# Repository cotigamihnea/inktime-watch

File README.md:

# InkTime Smartwatch - Proiect Hardware

Acesta este repository-ul oficial pentru dezvoltarea hardware a proiectului InkTime, un smartwatch bazat pe tehnologia E-Paper și procesorul nRF52840, optimizat pentru un consum redus de energie.

---

## 1. Diagramă Bloc

---

## 2. Bill of Materials (BOM) Principale

Mai jos sunt listate componentele integrate (IC) principale folosite în designul acestui smartwatch. Fișierul BOM complet cu toate componentele pasive (rezistențe, condensatoare) se găsește în folderul `Manufacturing`.

| Componentă / Modul | Rol în Sistem | JLC Parts Link | Datasheet |
| :--- | :--- | :--- | :--- |
| **nRF52840-QIAA** | Microcontroller Principal (BLE 5.0) | [C209930](https://jlcpcb.com/partdetail/Nordic_Semiconductor-nRF52840_QIAAR/C209930) | [Datasheet nRF52840](https://infocenter.nordicsemi.com/pdf/nRF52840_PS_v1.1.pdf) |
| **BQ25180YBGR** | Li-Ion Battery Charger (PMIC) | [C3005391](https://jlcpcb.com/partdetail/TexasInstruments-BQ25180YBGR/C3005391) | [Datasheet BQ25180](https://www.ti.com/lit/ds/symlink/bq25180.pdf) |
| **MAX17048G+T10** | Fuel Gauge (Monitorizare Baterie) | [C137599](https://jlcpcb.com/partdetail/Maxim_Integrated-MAX17048GT10/C137599) | [Datasheet MAX17048](https://datasheets.maximintegrated.com/en/ds/MAX17048-MAX17049.pdf) |
| **BMA421** | IMU / Accelerometru (Pedometer) | [C456073](https://jlcpcb.com/partdetail/Bosch-BMA421/C456073) | [Datasheet BMA421](https://www.bosch-sensortec.com/media/boschsensortec/downloads/datasheets/bst-bma421-fl000.pdf) |
| **503480-2400** | Conector Display E-Paper (24 pini) | [C265215](https://jlcpcb.com/partdetail/Molex-5034802400/C265215) | [Datasheet Molex](https://www.molex.com/pdm_docs/sd/5034802400_sd.pdf) |

---

## 3. Descrierea Funcționalității Hardware

Proiectul InkTime este gândit ca un wearable ultra-low-power. Arhitectura hardware este împărțită în următoarele module principale:

* **Unitatea de Procesare și Comunicație (nRF52840):** Este "creierul" plăcii. Acesta conține un nucleu ARM Cortex-M4F și un modul radio Bluetooth Low Energy (BLE 5.0). Microcontroller-ul gestionează toate perifericele și permite sincronizarea datelor cu un smartphone.
* **Afișajul (E-Paper Display):** Conectat printr-o interfață **SPI**, display-ul E-paper a fost ales pentru consumul său zero de energie în starea de repaus (consumă curent doar la refresh-ul ecranului). Circuitul său include o sursă de tensiune dedicată, cu o bobină și diode, comandată de un tranzistor DMG2305UX, pentru a-i asigura tensiunile specifice de operare.
* **Managementul Energiei (Power Management):** * **BQ25180:** Se ocupă de încărcarea sigură a bateriei Li-Po de la mufa USB (5V), setând curenți mici de încărcare adecvați bateriilor de smartwatch.
    * **MAX17048 (Fuel Gauge):** Citește tensiunea bateriei și calculează procentul (State of Charge - SoC) folosind algoritmul ModelGauge. Ambele comunică cu nRF-ul prin magistrala **I2C**.
* **Senzori și Haptic:** Accelerometrul **BMA421** este folosit pentru detectarea mișcării (ex: ridicarea mâinii pentru a aprinde ecranul) și numărarea pașilor, comunicând tot prin **I2C**. Pentru feedback tactil s-a integrat un driver haptic.
* **Considerații de Consum:** Designul este centrat pe eficiență. nRF52840 va sta majoritatea timpului în *Deep Sleep* (câțiva microamperi), trezindu-se doar la întreruperi generate de BMA421 (mișcare) sau la intervale regulate pentru a actualiza ecranul prin SPI.

---

## 4. Pinout nRF52840 (Alocarea Pinilor)

Microcontroller-ul comunică cu restul modulelor folosind interfețe digitale standardizate. Magistrala I2C este partajată pentru a economisi pini.

| Periferic / Modul | Pini nRF52840 Alocați | Interfață | Motiv / Funcție |
| :--- | :--- | :--- | :--- |
| **Magistrala I2C (Comună)** | `P0.11` (SDA), `P0.12` (SCL) | I2C | Folosită pentru BQ25180 (Charger), MAX17048 (Baterie) și BMA421 (IMU). I2C permite legarea mai multor senzori pe doar 2 pini fizici, reducând complexitatea rutării. |
| **BMA421 (Senzor Mișcare)**| `P0.13` (INT1) | GPIO | Pin de întrerupere pentru a „trezi” procesorul din sleep când utilizatorul face o mișcare bruscă. |
| **Display E-Paper** | `P1.01` (MOSI), `P1.02` (SCK), `P1.03` (CS) | SPI | Interfață de mare viteză unidirecțională pentru a trimite pixelii către ecran rapid. |
| **Control E-Paper** | `P1.04` (DC), `P1.05` (RST), `P1.06` (BUSY)| GPIO | Pini de control pentru stările ecranului (Data/Command, Reset și monitorizarea stării de Busy în timpul refresh-ului). |
| **Alimentare E-Paper** | `P0.06` | GPIO | Controlează tranzistorul care taie complet alimentarea ecranului când nu este folosit, salvând energie. |

*(Notă: Pinii exacți au fost aleși pentru a facilita cel mai scurt drum de rutare (Placement Optimization) pe PCB).*

---

## 5. Design Log & Renders

**Jurnal de Design:**
Proiectarea PCB-ului a presupus mai multe provocări:
1.  **Placement:** Componentele au fost grupate în "cartiere" logice: RF-ul sus în jurul antenei pentru a minimiza interferențele, IC-urile de Power Management lângă conectorul bateriei/USB, iar componentele digitale centralizate în jurul procesorului nRF52840.
2.  **Routing:** Datorită densității mari de pe o placă cu factor de formă mic (Smartwatch), am utilizat un mix de rutare manuală pentru traseele sensibile și Autorouter pentru optimizarea conexiunilor logice, obținând o rată de conectare excelentă pentru un sistem cu doar 2 straturi.

**Randări PCB:**

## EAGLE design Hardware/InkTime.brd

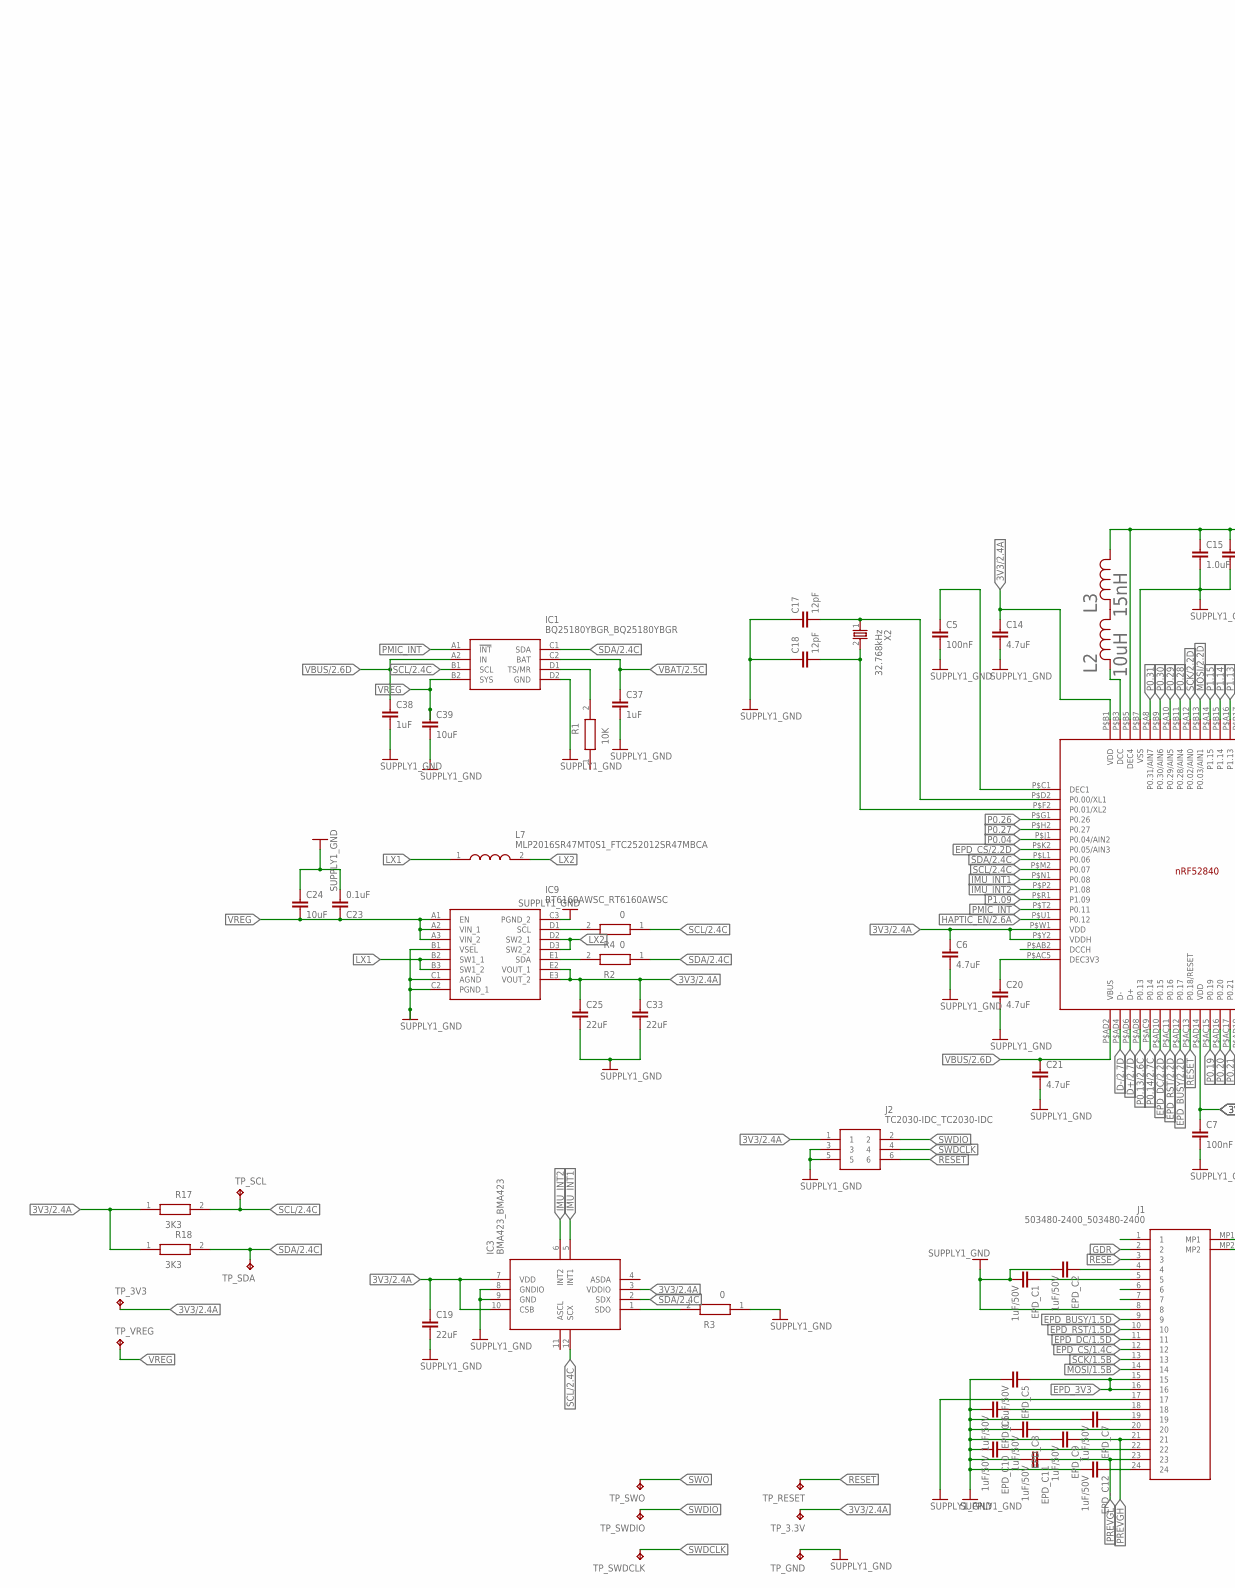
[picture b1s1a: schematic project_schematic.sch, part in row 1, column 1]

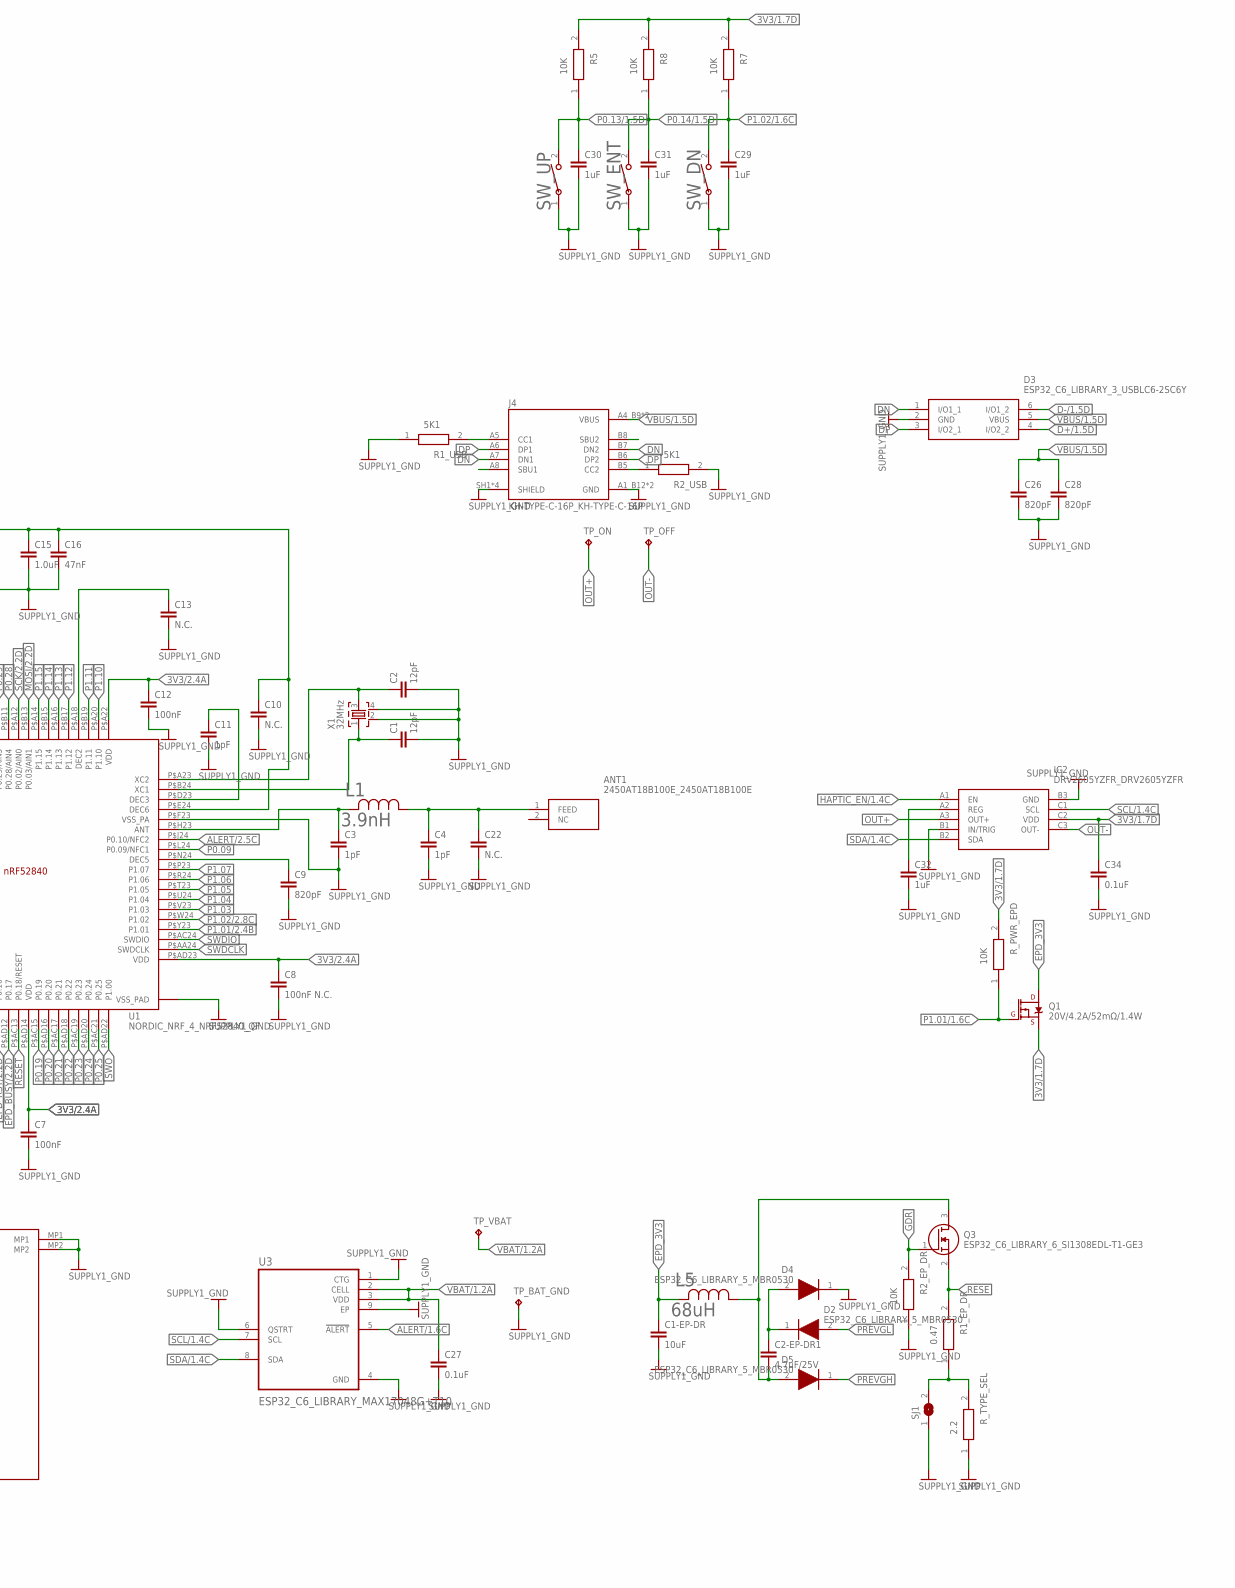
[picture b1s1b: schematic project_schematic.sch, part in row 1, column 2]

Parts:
ANT1: 2450AT18B100E_2450AT18B100E; 2450AT18B100E_ANTC3216X140N
C1, C2, C17, C18: 12pF; ESP32_C6_LIBRARY_1_ESP32_WROVER_EAGLE-LTSPICE_C0402
C1-EP-DR, C24, C39: 10uF; ESP32_C6_LIBRARY_1_ESP32_WROVER_EAGLE-LTSPICE_C0402
C2-EP-DR1: 4.7uF/25V; ESP32_C6_LIBRARY_1_ESP32_WROVER_EAGLE-LTSPICE_C0402
C3, C4, C11: 1pF; ESP32_C6_LIBRARY_1_ESP32_WROVER_EAGLE-LTSPICE_C0402
C5, C7, C12: 100nF; ESP32_C6_LIBRARY_1_ESP32_WROVER_EAGLE-LTSPICE_C0402
C6, C14, C20, C21: 4.7uF; ESP32_C6_LIBRARY_1_ESP32_WROVER_EAGLE-LTSPICE_C0402
C8: 100nF N.C.; ESP32_C6_LIBRARY_1_ESP32_WROVER_EAGLE-LTSPICE_C0402
C9, C26, C28: 820pF; ESP32_C6_LIBRARY_1_ESP32_WROVER_EAGLE-LTSPICE_C0402
C10, C13, C22: N.C.; ESP32_C6_LIBRARY_1_ESP32_WROVER_EAGLE-LTSPICE_C0402
C15: 1.0uF; ESP32_C6_LIBRARY_1_ESP32_WROVER_EAGLE-LTSPICE_C0402
C16: 47nF; ESP32_C6_LIBRARY_1_ESP32_WROVER_EAGLE-LTSPICE_C0402
C19, C25, C33: 22uF; ESP32_C6_LIBRARY_1_ESP32_WROVER_EAGLE-LTSPICE_C0402
C23, C27, C34: 0.1uF; ESP32_C6_LIBRARY_1_ESP32_WROVER_EAGLE-LTSPICE_C0402
C29, C30, C31, C32, C37, C38: 1uF; ESP32_C6_LIBRARY_1_ESP32_WROVER_EAGLE-LTSPICE_C0402
D2, D4, D5: ESP32_C6_LIBRARY_5_MBR0530; ESP32_C6_LIBRARY_5_SOD3716X135N
D3: ESP32_C6_LIBRARY_3_USBLC6-2SC6Y; ESP32_C6_LIBRARY_3_SOT95P280X145-6N
EPD_C1, EPD_C2, EPD_C6, EPD_C7, EPD_C8, EPD_C9, EPD_C10, EPD_C11, EPD_C12: 1uF/50V; ESP32_C6_LIBRARY_1_ESP32_WROVER_EAGLE-LTSPICE_C0402
EPD_C5: 0.1uF/50V; ESP32_C6_LIBRARY_1_ESP32_WROVER_EAGLE-LTSPICE_C0402
IC1: BQ25180YBGR_BQ25180YBGR; BQ25180YBGR_BGA8C40P2X4_100X155X50
IC2: DRV2605YZFR_DRV2605YZFR; DRV2605YZFR_BGA9C50P3X3_144X144X62
IC3: BMA423_BMA423
IC9: RT6160AWSC_RT6160AWSC; RT6160AWSC_BGA15C40P3X5_140X230X60
J1: 503480-2400_503480-2400; 503480-2400_5034802400
J2: TC2030-IDC_TC2030-IDC; TC2030-IDC_TC2030IDC
J4: KH-TYPE-C-16P_KH-TYPE-C-16P; KH-TYPE-C-16P_KINGHELM_KH-TYPE-C-16P
L1: 3.9nH; ESP32_C6_LIBRARY_2_IND_4828-WE-TPC_WRE
L2: 10uH; ESP32_C6_LIBRARY_2_IND_4828-WE-TPC_WRE
L3: 15nH; ESP32_C6_LIBRARY_2_IND_4828-WE-TPC_WRE
L5: 68uH; ESP32_C6_LIBRARY_2_IND_4828-WE-TPC_WRE
L7: MLP2016SR47MT0S1_FTC252012SR47MBCA; MLP2016SR47MT0S1_INDC2016X100N
Q1: 20V/4.2A/52mΩ/1.4W; ESP32_C6_LIBRARY_4_ESP32_C6_LIBRARY_4_ESP32_C6_LIBRARY_4_ES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
Q3: ESP32_C6_LIBRARY_6_SI1308EDL-T1-GE3; ESP32_C6_LIBRARY_6_SOT65P210X110-3N
R1, R2_EP_DR, R5, R7, R8: 10K; CPF0201D7K68C1_0201
R1_EP_DR: 0.47; CPF0201D7K68C1_0201
R1_USB, R2_USB: 5K1; CPF0201D7K68C1_0201
R2, R3, R4: 0; CPF0201D7K68C1_0201
R17, R18: 3K3; CPF0201D7K68C1_0201
R_PWR_EPD: 10K; CPF0201D7K68C1_0201
R_TYPE_SEL: 2.2; CPF0201D7K68C1_0201
SJ1: ESP32_C6_LIBRARY_7_JUMPER_SJ
SW_DN: 2025-10-22_07-23-44_LIBRARY_EVP-AKE31ASW_EVP-AKE3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; 2025-10-22_07-23-44_LIBRARY_SW_EVP-AKE31A_PAN
SW_ENT: 2025-10-22_07-23-44_LIBRARY_EVP-AKE31ASW_EVP-AKE3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; 2025-10-22_07-23-44_LIBRARY_SW_EVP-AKE31A_PAN
SW_UP: 2025-10-22_07-23-44_LIBRARY_EVP-AKE31ASW_EVP-AKE3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; 2025-10-22_07-23-44_LIBRARY_SW_EVP-AKE31A_PAN
TP_3.3V, TP_3V3: HECTOR_WATCH_1_TPTP20R; HECTOR_WATCH_1_TP20R
TP_BAT_GND: HECTOR_WATCH_1_TPTP20R; HECTOR_WATCH_1_TP20R
TP_GND: HECTOR_WATCH_1_TPTP20R; HECTOR_WATCH_1_TP20R
TP_OFF: HECTOR_WATCH_1_TPTP20R; HECTOR_WATCH_1_TP20R
TP_ON: HECTOR_WATCH_1_TPTP20R; HECTOR_WATCH_1_TP20R
TP_RESET: HECTOR_WATCH_1_TPTP20R; HECTOR_WATCH_1_TP20R
TP_SCL: HECTOR_WATCH_1_TPTP20R; HECTOR_WATCH_1_TP20R
TP_SDA: HECTOR_WATCH_1_TPTP20R; HECTOR_WATCH_1_TP20R
TP_SWDCLK: HECTOR_WATCH_1_TPTP20R; HECTOR_WATCH_1_TP20R
TP_SWDIO: HECTOR_WATCH_1_TPTP20R; HECTOR_WATCH_1_TP20R
TP_SWO: HECTOR_WATCH_1_TPTP20R; HECTOR_WATCH_1_TP20R
TP_VBAT: HECTOR_WATCH_1_TPTP20R; HECTOR_WATCH_1_TP20R
TP_VREG: HECTOR_WATCH_1_TPTP20R; HECTOR_WATCH_1_TP20R
U1: NORDIC_NRF_4_NRF52840_QF; NORDIC_NRF_4_AQFN50P700X700X85_HS-74N
U3: ESP32_C6_LIBRARY_MAX17048G+T10; ESP32_C6_LIBRARY_SON50P200X200X80-9N
X1: 32MHz; NORDIC_NRF_BT-XTAL_2016_N
X2: 32.768kHz; NORDIC_NRF_1_XTAL_3215_N

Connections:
3V3/1.7D: C34.1, IC2.C2 (VDD), Q1.2 (S), R5.2, R7.2, R8.2, R_PWR_EPD.2
3V3/2.4A: C6.1, C7.1, C8.1, C12.1, C14.1, C19.1, C25.1, C33.1, IC3.3 (VDDIO), IC3.7 (VDD), IC3.10 (CSB), IC9.E2 (VOUT_1), IC9.E3 (VOUT_2), J2.1, R17.1, R18.1, TP_3.3V.TP, TP_3V3.TP, U1.P$A22 (VDD), U1.P$AD14 (VDD), U1.P$AD23 (VDD), U1.P$B1 (VDD), U1.P$W1 (VDD), U1.P$Y2 (VDDH)
ALERT/1.6C: U3.5 (!ALERT)
ALERT/2.5C: U1.P$J24 (P0.10/NFC2)
D+/1.5D: D3.4 (I/O2_2)
D+/2.7D: U1.P$AD6 (D+)
D-/1.5D: D3.6 (I/O1_2)
D-/2.7D: U1.P$AD4 (D-)
DN: D3.1 (I/O1_1), J4.A7 (DN1), J4.B7 (DN2)
DP: D3.3 (I/O2_1), J4.A6 (DP1), J4.B6 (DP2)
EPD_3V3: C1-EP-DR.1, EPD_C5.1, J1.15, J1.16, L5.2, Q1.3 (D)
EPD_BUSY/1.5D: J1.9
EPD_BUSY/2.2D: U1.P$AD12 (P0.17)
EPD_CS/1.4C: J1.12
EPD_CS/2.2D: U1.P$K2 (P0.05/AIN3)
EPD_DC/1.5D: J1.11
EPD_DC/2.2D: U1.P$AD10 (P0.15)
EPD_RST/1.5D: J1.10
EPD_RST/2.2D: U1.P$AC11 (P0.16)
GDR: J1.2, Q3.1 (G), R2_EP_DR.2
GND: C1.2, C1-EP-DR.2, C2.2, C3.2, C4.2, C5.2, C6.2, C7.2, C8.2, C9.2, C10.2, C11.2, C12.2, C13.2, C14.2, C15.2, C16.2, C17.1, C18.1, C19.2, C20.2, C21.2, C22.2, C23.2, C24.1, C25.2, C26.2, C27.2, C28.2, C29.2, C30.2, C31.2, C32.2, C33.2, C34.2, C37.2, C38.2, C39.2, D3.2 (GND), D4.1 (K), EPD_C1.2, EPD_C2.2, EPD_C5.2, EPD_C6.2, EPD_C7.2, EPD_C8.2, EPD_C9.2, EPD_C10.2, EPD_C11.2, EPD_C12.2, IC1.D2 (GND), IC2.B1 (IN/TRIG), IC2.B3 (GND), IC3.8 (GNDIO), IC3.9 (GND), IC9.B1 (VSEL), IC9.C1 (AGND), IC9.C2 (PGND_1), IC9.C3 (PGND_2), J1.8, J1.17, J1.MP1, J1.MP2, J2.3, J2.5, J4.A1_B12 (GND), J4.A12_B1 (GND), J4.SH1 (SHIELD), J4.SH2 (SHIELD), J4.SH3 (SHIELD), J4.SH4 (SHIELD), R1_USB.1, R2_EP_DR.1, R2_USB.2, R3.1, R_TYPE_SEL.1, SJ1.1, SW_DN.1, SW_ENT.1, SW_UP.1, TP_BAT_GND.TP, TP_GND.TP, U1.P$74 (VSS_PAD), U1.P$75 (VSS_PAD), U1.P$76 (VSS_PAD), U1.P$77 (VSS_PAD), U1.P$78 (VSS_PAD), U1.P$79 (VSS_PAD), U1.P$80 (VSS_PAD), U1.P$81 (VSS_PAD), U1.P$82 (VSS_PAD), U1.P$83 (VSS_PAD), U1.P$84 (VSS_PAD), U1.P$85 (VSS_PAD), U1.P$86 (VSS_PAD), U1.P$87 (VSS_PAD), U1.P$88 (VSS_PAD), U1.P$89 (VSS_PAD), U1.P$90 (VSS_PAD), U1.P$B7 (VSS), U1.P$F23 (VSS_PA), U3.1 (CTG), U3.4 (GND), U3.6 (QSTRT), U3.9 (EP), X1.2, X1.4
HAPTIC_EN/1.4C: IC2.A1 (EN)
HAPTIC_EN/2.6A: U1.P$U1 (P0.12)
IMU_INT1: IC3.5 (INT1), U1.P$N1 (P0.08)
IMU_INT2: IC3.6 (INT2), U1.P$P2 (P1.08)
LX1: IC9.B2 (SW1_1), IC9.B3 (SW1_2), L7.1
LX2: IC9.D2 (SW2_1), IC9.D3 (SW2_2), L7.2
MOSI/1.5B: J1.14
MOSI/2.2D: U1.P$A14 (P1.15)
unnamed: IC9.D1 (SCL), R4.2
unnamed: IC9.E1 (SDA), R2.2
unnamed: L2.2, U1.P$B3 (DCC)
unnamed: L2.1, L3.2
unnamed: C17.2, U1.P$D2 (P0.00/XL1), X2.1
unnamed: IC1.D1 (TS/MR), R1.2
unnamed: IC3.1 (SDO), R3.2
unnamed: ANT1.1 (FEED), C4.1, C22.1, L1.1
unnamed: C3.1, L1.2, U1.P$H23 (ANT)
unnamed: C1.1, U1.P$B24 (XC1), X1.1
unnamed: C2.1, U1.P$A23 (XC2), X1.3
unnamed: J4.A5 (CC1), R1_USB.2
unnamed: EPD_C2.1, J1.4
unnamed: EPD_C1.1, J1.5
unnamed: C13.1, U1.P$A18 (DEC2)
unnamed: C2-EP-DR1.2, D5.2 (A), L5.1, Q3.3 (D)
unnamed: C2-EP-DR1.1, D2.1 (K), D4.2 (A)
unnamed: C11.1, U1.P$D23 (DEC3)
unnamed: C10.1, C15.1, C16.1, L3.1, U1.P$B5 (DEC4), U1.P$E24 (DEC6)
unnamed: J4.B5 (CC2), R2_USB.1
unnamed: C9.1, U1.P$N24 (DEC5)
unnamed: C32.1, IC2.A2 (REG)
unnamed: EPD_C6.1, J1.18
unnamed: EPD_C7.1, J1.19
unnamed: EPD_C8.1, J1.20
unnamed: EPD_C10.1, J1.22
unnamed: R1_EP_DR.1, R_TYPE_SEL.2, SJ1.2
unnamed: EPD_C12.1, J1.24
unnamed: C20.1, U1.P$AC5 (DEC3V3)
unnamed: C18.2, U1.P$F2 (P0.01/XL2), X2.2
unnamed: C5.1, U1.P$C1 (DEC1)
OUT+: IC2.A3 (OUT+), TP_ON.TP
OUT-: IC2.C3 (OUT-), TP_OFF.TP
P0.04: U1.P$J1 (P0.04/AIN2)
P0.09: U1.P$L24 (P0.09/NFC1)
P0.13/1.5D: C30.1, R5.1, SW_UP.2
P0.13/2.6C: U1.P$AD8 (P0.13)
P0.14/1.5D: C31.1, R8.1, SW_ENT.2
P0.14/2.7C: U1.P$AC9 (P0.14)
P0.19: U1.P$AC15 (P0.19)
P0.20: U1.P$AD16 (P0.20)
P0.21: U1.P$AC17 (P0.21)
P0.22: U1.P$AD18 (P0.22)
P0.23: U1.P$AC19 (P0.23)
P0.24: U1.P$AD20 (P0.24)
P0.25: U1.P$AC21 (P0.25)
P0.26: U1.P$G1 (P0.26)
P0.27: U1.P$H2 (P0.27)
P0.28: U1.P$A12 (P0.02/AIN0)
P0.29: U1.P$B11 (P0.28/AIN4)
P0.30: U1.P$A10 (P0.29/AIN5)
P0.31: U1.P$B9 (P0.30/AIN6)
P1.01/1.6C: Q1.1 (G), R_PWR_EPD.1
P1.01/2.4B: U1.P$Y23 (P1.01)
P1.02/1.6C: C29.1, R7.1, SW_DN.2
P1.02/2.8C: U1.P$W24 (P1.02)
P1.03: U1.P$V23 (P1.03)
P1.04: U1.P$U24 (P1.04)
P1.05: U1.P$T23 (P1.05)
P1.06: U1.P$R24 (P1.06)
P1.07: U1.P$P23 (P1.07)
P1.09: U1.P$R1 (P1.09)
P1.10: U1.P$A20 (P1.10)
P1.11: U1.P$B19 (P1.11)
P1.12: U1.P$B17 (P1.12)
P1.14: U1.P$A16 (P1.13)
P1.15: U1.P$B15 (P1.14)
PMIC_INT: IC1.A1 (!INT), U1.P$T2 (P0.11)
PREVGH: D5.1 (K), EPD_C9.1, J1.21
PREVGL: D2.2 (A), EPD_C11.1, J1.23
RESE: J1.3, Q3.2 (S), R1_EP_DR.2
RESET: J2.6, TP_RESET.TP, U1.P$AC13 (P0.18/RESET)
SCK/1.5B: J1.13
SCK/2.2D: U1.P$B13 (P0.03/AIN1)
SCL/1.4C: IC2.C1 (SCL), U3.7 (SCL)
SCL/2.4C: IC1.B1 (SCL), IC3.12 (SCX), R4.1, R17.2, TP_SCL.TP, U1.P$M2 (P0.07)
SDA/1.4C: IC2.B2 (SDA), U3.8 (SDA)
SDA/2.4C: IC1.C1 (SDA), IC3.2 (SDX), R2.1, R18.2, TP_SDA.TP, U1.P$L1 (P0.06)
SWDCLK: J2.4, TP_SWDCLK.TP, U1.P$AA24 (SWDCLK)
SWDIO: J2.2, TP_SWDIO.TP, U1.P$AC24 (SWDIO)
SWO: TP_SWO.TP, U1.P$AD22 (P1.00)
VBAT/1.2A: C27.1, TP_VBAT.TP, U3.2 (CELL), U3.3 (VDD)
VBAT/2.5C: C37.1, IC1.C2 (BAT)
VBUS/1.5D: C26.1, C28.1, D3.5 (VBUS), J4.A4_B9 (VBUS), J4.A9_B4 (VBUS)
VBUS/2.6D: C21.1, C38.1, IC1.A2 (IN), U1.P$AD2 (VBUS)
VREG: C23.1, C24.2, C39.1, IC1.B2 (SYS), IC9.A1 (EN), IC9.A2 (VIN_1), IC9.A3 (VIN_2), TP_VREG.TP

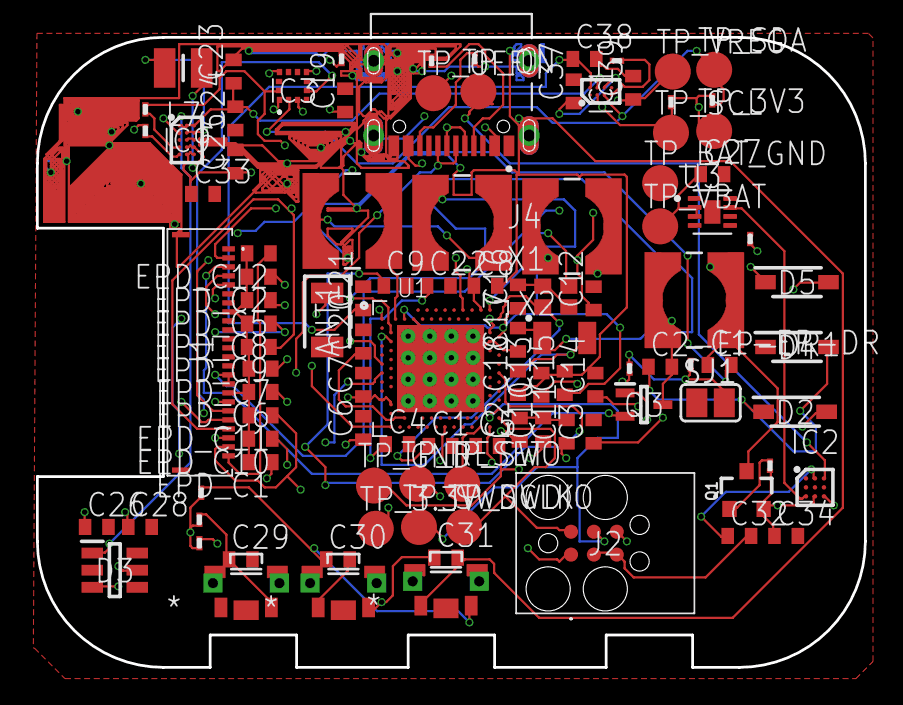
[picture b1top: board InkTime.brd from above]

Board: 4 copper layers, 46.0 x 35.0 mm, 105 parts (0 on the bottom side), 65 nets.

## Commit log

2026-04-10 added licese
2026-04-10 updated license
2026-04-10 readme
2026-04-10 schelet proiect
2026-04-10 fisiere de pana acm
2026-04-10 added routes
2026-04-10 added smth
2026-04-10 poze
2026-04-10 manu done
2026-04-10 done temporary
2026-04-10 3d file
2026-04-20 issue solved
2026-04-20 pdf added

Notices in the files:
parts and their libraries:
COPYRIGHT: Copyright (C) 2024 Ultra Librarian. All rights reserved.
COPYRIGHT: Copyright (C) 2025 Ultra Librarian. All rights reserved.
